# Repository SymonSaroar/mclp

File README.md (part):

# MCLP load-cell core

`mclp_core` is a load-cell weighing IP core for AMD FPGAs. It reads 1 to 64 Analog Devices AD7190 24-bit
sigma-delta ADCs in parallel, one per load cell, and computes the weight in the FPGA. The core decimates each
channel, corrects it for offset and gain, and trims it for its position on the platform. Then it sums the
channels and low-pass filters the sum. Software configures the core and reads the weight over AXI4-Lite. Raw
per-channel samples stream out over AXI4-Stream for calibration and diagnostics.

An optional inference engine runs a small int8 neural network on each weigh-in-motion load and corrects the
result. Software loads its models over AXI4-Lite at run time.

The repository also contains:

- A reference design for the AMD ZC702 evaluation board (Zynq-7000): Vivado block design, PetaLinux image,
  console application and REST/MQTT service
- An 8-channel AD7190 FMC card in KiCad: [hw/adc-card](hw/adc-card/README.md)
- cocotb unit tests, a system test with AD7190 models, and a DMA test of the reference design

Status: passes simulation at 1, 8 and 64 channels. Not tested on hardware yet.

## License

MCLP is available under the CERN Open Hardware Licence Version 2 - Strongly Reciprocal (hardware) and the
GPL-3.0 (software in `sw/`), or under a paid commercial license. See [LICENSE](LICENSE).

## Features

- Up to 64 channels
- Simultaneous sampling of all channels
- Up to 4800 samples/s per channel
- Weight output rate programmable up to 600 Hz
- Per-channel offset, gain and corner-trim calibration
- 64-tap FIR filter, coefficients reloadable at run time
- Stability detection
- Weigh-in-motion
- Int8 neural-network inference on each weigh-in-motion load, models loadable at run time
- Overload detection
- Per-channel fault detection: open wire, missing excitation, over-range, data errors
- Raw data capture, continuous or triggered
- Built-in self-test
- AXI4-Lite control interface
- AXI4-Stream raw data interface
- Interrupt output

## Supported devices and tools

- FPGA families declared in the IP package: Zynq-7000, Spartan-7, Artix-7, Kintex-7, Virtex-7, Kintex and
  Virtex UltraScale and UltraScale+, Zynq UltraScale+ MPSoC. Implemented and timed on `xc7z020clg484-1` only.
- Vivado 2025.1. The reference block-design script refuses other versions.
- Simulators: Vivado simulator, and Icarus Verilog 12 with the XPM models in `tb/common/xpm_models.sv`
- ADC: AD7190

## Resource utilization

`N_CH = 8`, `USE_NN = 1`, out-of-context synthesis, `xc7z020clg484-1`, Vivado 2025.1:

| LUT | LUT as memory | FF | Block RAM tiles | DSP48E1 |
|---|---|---|---|---|
| 5252 | 252 | 7319 | 18.5 (17 RAMB36, 3 RAMB18) | 23 |

Of that, the placed datapath of the inference engine takes 1641 LUTs, 758 FFs, 1 RAMB36, 1 RAMB18 and 10
DSP48E1. Its model memories are in the register file.

The reference design runs on the -1 speed grade with `aclk` at 100 MHz, `clk_spi` at 20 MHz and `clk_dsp` at
50 MHz. All user-specified timing constraints are met: WNS +0.737 ns, WHS +0.021 ns.

## Getting started

### Add the core to a Vivado project

1. Get the packaged core. Download `mclp_core-2.0.zip` from the [releases page](../../releases) and unzip it,
   or package it from this repository:

   ```sh
   vivado -mode batch -source tcl/package_ip.tcl      # writes build/ip_repo/mclp_core
   ```

2. Add the folder that holds `mclp_core` to the project's IP repositories (Settings > IP > Repository).
3. Add MCLP load-cell core to a block design. Set Channels (`N_CH`) and Inference engine (`USE_NN`).
4. Connect the interfaces:

   | Core | Connect to |
   |---|---|
   | `s_axi` | AXI4-Lite master, 64 KB address range |
   | `m_axis_raw` | AXI DMA S2MM, 64-bit stream. Optional. With `tready` low, the core drops raw records and the weight path keeps running. |
   | `aclk`, `aresetn` | AXI clock and its reset |
   | `clk_spi`, `clk_dsp`, `clk_locked` | MMCM outputs at 20 MHz and 50 MHz, and its `locked`. Reset the MMCM from the AXI reset. |
   | `irq` | Interrupt controller |
   | `spi_*`, `adc_sync_n` | FPGA pins to the AD7190s |

   [tcl/mclp_top_bd.tcl](tcl/mclp_top_bd.tcl) builds the reference block design with these connections.

5. Constrain the ADC pins: package pins, an I/O standard that matches the AD7190 DVDD, and the false paths in
   [xdc/mclp_timing.xdc](xdc/mclp_timing.xdc). The XPM macros inside the core carry their own clock-domain
   crossing constraints.
6. Write the software against the [register space](#register-space) and the
   [programming sequence](#programming-sequence). `sw/common` is a C implementation for bare metal and Linux.

### Prototype on the ZC702

The [reference design](#reference-design-zc702) runs the core with 8 channels on a ZC702 with the FMC card.
Each release has prebuilt boot files for it.

## Product specification

### Block diagram

### Parameters

| Parameter | Values | Default | Description |
|---|---|---|---|
| `N_CH` | 1 to 64 | 8 | Number of AD7190 chips, and the width of `spi_sdi` |
| `USE_NN` | 0, 1 | 1 | Inference engine and its model memories |

### Ports

| Port | Dir | Width | Clock | Description |
|---|---|---|---|---|
| `aclk` | in | 1 | | AXI clock |
| `aresetn` | in | 1 | async | Reset, active low |
| `clk_spi` | in | 1 | | 20 MHz: SPI master, sequencer, loopback emulator |
| `clk_dsp` | in | 1 | | 50 MHz: processing chain, raw capture |
| `clk_locked` | in | 1 | async | `clk_spi` and `clk_dsp` run. Holds their domains in reset while low. |
| `s_axi_*` | | | `aclk` | AXI4-Lite slave, 16-bit address, 32-bit data |
| `m_axis_raw_*` | out | 64 | `aclk` | AXI4-Stream master: `tdata`, `tlast`, `tvalid`, `tready` |
| `irq` | out | 1 | `aclk` | Interrupt, level, active high |
| `spi_sclk` | out | 1 | `clk_spi` | SPI clock, to SCLK of every AD7190 |
| `spi_sdo` | out | 1 | `clk_spi` | SPI data out, to DIN of every AD7190 |
| `spi_cs_n` | out | 1 | `clk_spi` | Chip select, to CS of every AD7190 |
| `adc_sync_n` | out | 1 | `clk_spi` | Filter reset, to SYNC of every AD7190 |
| `spi_sdi` | in | `N_CH` | async | SPI data in, bit k from DOUT/RDY of AD7190 k. Its falling edge marks data ready. |

### Clocks and resets

| Clock | Frequency | Logic |
|---|---|---|
| `aclk` | 100 MHz tested | AXI interfaces, registers, interrupt |
| `clk_spi` | 20 MHz required | SPI master, sequencer, loopback emulator, timestamps |
| `clk_dsp` | 50 MHz tested | CIC, scaling, sum, FIR, stability, weigh-in-motion, raw capture, inference |

SCLK is `clk_spi` / 8. A SYNC pulse lasts 32 `clk_spi` cycles (1.6 µs). The sequencer's `WAIT_US` counts 20
cycles per microsecond.

`aresetn` resets the `aclk` logic, and `clk_locked` resets the `clk_spi` and `clk_dsp` logic. Both are
asynchronous, and the core synchronizes them. Hold `clk_locked` low while `aresetn` is low. An MMCM reset
driven by the AXI reset does this.

### Data path

| Stage | Operation | Rate | Width |
|---|---|---|---|
| AD7190 | continuous conversion, sinc4, FS = 1, chop off | 4800 Hz | 24 data + 8 status |
| SPI receive | `N_CH` lanes in parallel, offset binary to two's complement | 4800 Hz | 24 |
| CIC | R = 8, N = 3, gain 256 per ADC code | 600 Hz | 32 |
| Gain/offset | `sat32(((x - OFFSET) * GAIN) >>> 30)` | 600 Hz | 32 |
| Trim | `sat32((x * TRIM) >>> 30)` | 600 Hz | 32 |
| Sum | exact sum of `N_CH` channels | 600 Hz | 40 |
| FIR | 64 taps, 18-bit coefficients, full precision | 600 Hz | 64 |
| Weight | `sat32(FIR >>> (20 + ceil(log2(N_CH))))` | 600 Hz | 32 |
| RESULT | every RESULT_DECIM-th weight | 50 Hz | 32 |

The default FIR is a 12 Hz Hamming-windowed sinc with taps summing to 2^20 (`coeff/fir64.py`). Its group
delay is 31.5 samples, 52.5 ms. At unity gain and trim, RESULT changes by 256 / 2^ceil(log2(N_CH)) counts per
ADC code on one channel: 32 at 8 channels. All channels at full scale fit in 32 bits.

The stability flag rises after STAB_COUNT consecutive weights within ±STAB_BAND of a reference. A weight
outside the band clears the flag and becomes the new reference.

A weigh-in-motion load starts with the first weight above WIM_ENTER and ends at the first weight below
WIM_EXIT. The core sums the load's weights that are at or above WIM_LEVEL times its peak. The ramps on and off
the platform drop out at any speed. The result is WIM_SUM / WIM_COUNT, one per load. The core holds the last
1024 weights of a load (1.7 s). In a longer load, it compares each older weight with the peak up to 1024
weights later.

### Register space

The register space is 64 KB. Offsets are from the base address that the block design assigns (0x43C0_0000 in
the reference design). Register map version 5. Each per-channel array takes one 64-word block, with channel k
at +4k.

| Offset | Name | Description |
|---|---|---|
| 0x000 | ID | 0x4D4C_05nn. [31:16] 0x4D4C ("ML"), [15:8] register map version, [7:0] `N_CH` |
| 0x004 | CTRL | [0] enable (reset 1), [1] loopback, [5:4] raw_tap, [6] raw_enable. Self-clearing: [2] fir_reload, [3] seq_start, [7] sw_trigger, [8] fault_clear |
| 0x008 | STATUS | [0] clocks locked, [1] seq_busy, [2] reload_busy, [3] overload, [4] stable, [5] capture_active |
| 0x00C | IRQ_STATUS | Write 1 to clear. [0] result, [1] stable, [2] weigh-in-motion, [3] overload, [4] fault, [5] sequencer done, [6] capture done, [7] inference done |
| 0x010 | IRQ_ENABLE | Same bits as IRQ_STATUS |
| 0x020 | RESULT | Weight, signed |
| 0x024 | RESULT_SEQ | Increments with each RESULT update |
| 0x028, 0x02C | WIM_SUM_LO, WIM_SUM_HI | Weigh-in-motion sum, 64 bit |
| 0x030 | WIM_COUNT | Weigh-in-motion weights summed |
| 0x034 | STAB_BAND | Reset 4096 |
| 0x038 | STAB_COUNT | Reset 60 |
| 0x03C, 0x040 | WIM_ENTER, WIM_EXIT | Reset 0x7FFF_FFFF (off) |
| 0x048 | RESULT_DECIM | Reset 12 |
| 0x04C | TRIG_CFG | [1:0] mode: 0 continuous, 1 one-shot, 2 threshold. [31:16] frames per one-shot |
| 0x050 | TRIG_THRESHOLD | Sum level that starts a mode 2 capture |
| 0x054 | LOOPBACK_CFG | [0] ramp, [1] inject ERR, [2] inject parity error, [9:4] channel for injection, [31:16] frame period in `clk_spi` cycles (reset 4166) |
| 0x058 | LOOPBACK_VALUE | Constant-mode data, reset 0x123456 |
| 0x05C | WIM_LEVEL | [15:0] share of the load's peak, Q0.16. Reset 0xEE14 (0.93) |
| 0x200-0x2FC | FIR | 64 coefficients, word i applies to x[n-i]. Reset from `coeff/fir64.mem` |
| 0x400-0x7FC | SEQ | Sequencer RAM, 256 words. Reset from `coeff/seq_init.mem` |
| 0x800-0x8FC | SEQ_RESP[64] | Last XFER read per chip |
| 0x900-0x9FC | GAIN[64] | Q2.30, reset 1.0 |
| 0xA00-0xAFC | OFFSET[64] | CIC units, reset 0 |
| 0xB00-0xBFC | TRIM[64] | Q2.30, reset 1.0 |
| 0xC00-0xCFC | FAULT[64] | Sticky. [0] ERR, [1] NOREF, [2] parity error, [3] stale (RDY set), [4] loopback mismatch |
| 0x1000 | NN_CTRL | [0] enable: run the model after each weigh-in-motion load. Reset 0 |
| 0x1004 | NN_STATUS | [0] busy |
| 0x1008 | NN_SEQ | Increments with each inference |
| 0x100C | NN_EST | Corrected weigh-in-motion estimate, weight counts, signed |
| 0x1010 | NN_CORR | Correction to WIM_SUM / WIM_COUNT, Q0.20, signed |
| 0x1014 | NN_CYCLES | `clk_dsp` cycles of the last inference |
| 0x2000-0x20FC | NN_LAYER[64] | Layer list. Reset from `coeff/nn_layers.mem` |
| 0x3000-0x33FC | NN_BIAS[256] | Biases, int32. Reset from `coeff/nn_bias.mem` |
| 0x4000-0x7FFC | NN_WEIGHT[4096] | Weights, four int8 per word, the first in [7:0]. Reset from `coeff/nn_weights.mem` |

Unmapped addresses and array entries at or above `N_CH` read 0x0BAD_0BAD. With `USE_NN = 0`, 0x1000 to 0x7FFF
read 0x0BAD_0BAD too. A configuration write reaches `clk_spi` and `clk_dsp` within about 1 µs.

Fault flags:

- ERR is the AD7190's error bit: over-range, an open input with the burnout currents on, or a missing
  reference when REFDET is on.
- NOREF is its reference-detect bit.
- A parity error is a corrupted word on the cable.
- Stale means that the chip's conversion was not complete when the core read it.

A new flag sets IRQ_STATUS[4]. CTRL.fault_clear clears all flags.

### Sequencer

The sequencer drives the shared SPI lines from a command list in its RAM. It runs the list from word 0 after
reset, on CTRL.seq_start, and on a rising edge of CTRL.enable. Each command is two words:

```
w0 = {op[3:0], ntx[5:0], nrx[5:0], arg[15:0]}
w1 = data shifted out, MSB first
```

| op | Command | Action |
|---|---|---|
| 0 | END | Stop |
| 1 | XFER | Shift `ntx` bits of `w1` out, then read `nrx` bits from every chip into SEQ_RESP |
| 2 | SYNC | SYNC low for 1.6 µs |
| 3 | WAIT_US | Wait `arg` µs |
| 4 | WAIT_RDY | Wait for DOUT/RDY low on chip 0 |
| 5 | STREAM | Read a 32-bit word (data + status) from every chip on each DOUT/RDY falling edge |

STATUS.seq_busy falls and IRQ_STATUS[5] sets when the list reaches END or STREAM.

The default list (`coeff/seq_init.py`) resets the chips, reads their ID registers and writes the
configuration. Then it runs the internal zero-scale calibration, starts continuous conversion, pulses SYNC
and streams. The AD7190 configuration is AIN1/AIN2, REFIN1, reference detect on, buffer on, bipolar and gain
128. The clock and filter settings are the external clock on MCLK2, sinc4 and FS = 1, with the status byte
and parity appended to each word. To leave continuous read, run `WAIT_RDY`, then an `XFER` of 0x58 with
`ntx = 8`, `nrx = 32`.

### Raw records

CTRL.raw_tap selects the source: 0 ADC code (24 bit, sign-extended), 1 CIC output, 2 after gain/offset, 3
after trim. Each frame becomes one record of 2 + ceil(`N_CH` / 2) 64-bit words, with `tlast` on the last word.
A record is 48 bytes at 8 channels and 272 bytes at 64.

| Word | Content |
|---|---|
| 0 | [63:16] timestamp in `clk_spi` cycles at the DOUT/RDY edge, [15:14] tap, [13:0] 0 |
| 1 to ceil(`N_CH` / 2) | Samples `{ch1, ch0}`, `{ch3, ch2}` and so on, with `{0, chN-1}` last when `N_CH` is odd |
| last | Fault word: bit k set when channel k had a fault flag in this frame |

At tap 0, the timestamp and the fault word belong to the record's own frame. At taps 1 to 3, they come from
the newest complete frame. The core starts a record at channel 0 only when the output FIFO has room for the
whole record. Otherwise it skips the record.

Trigger modes (TRIG_CFG[1:0]):

- 0: continuous while CTRL.raw_enable is set.
- 1: a one-shot of TRIG_CFG[31:16] records after CTRL.sw_trigger.
- 2: a one-shot that CTRL.sw_trigger arms. It starts at the first frame whose sum exceeds TRIG_THRESHOLD.

IRQ_STATUS[6] sets when a one-shot ends.

### Inference engine

With `USE_NN = 1`, the core runs a small neural network on each weigh-in-motion load and corrects the result.
The engine starts when a load ends and NN_CTRL.enable is set. It skips a load that ends while it is busy.

The input is every 4th weight up to the load's exit sample: 256 weights, 1.7 s. Each weight x enters as its
deviation from the core's own result, ref = WIM_SUM / WIM_COUNT. The int8 input value is
(x / ref - 1) x 1024, saturated. In integers:

- ref is the quotient WIM_SUM / WIM_COUNT, clamped to 1 to 2^31 - 1.
- k is the bit length of ref, and R = 2^(k+21) / ref.
- d = x - ref, clamped to ±2^k.
- q = sat8((d x R + 2^(k+10)) >> (k+11)).

The network is a list of one-dimensional convolutions over the valid positions. Weights and activations are
int8, and biases are int32. A dense layer is a convolution whose kernel spans its whole input. Hidden layers
requantize to int8 as (acc x M + 2^(s-1)) >> s, with a 15-bit M, and clip at 0 when the layer has a ReLU. The
last layer's M and s scale its accumulator the same way to NN_CORR, a correction in Q0.20 saturated to 32
bits. The engine then computes NN_EST = ref + (ref x NN_CORR + 2^19) >> 20, saturated to 32 bits.

The engine does one multiply-accumulate per `clk_dsp` cycle. The default model takes 44439 cycles (0.89 ms at
50 MHz). IRQ_STATUS[7] sets when the result is in the registers.

The layer list has four words per layer, from NN_LAYER[0] to the layer marked last.

| Word | Fields |
|---|---|
| 0 | [31] last, [30] ReLU, [29:26] stride, [25:16] kernel K, [15:8] input channels C, [7:0] output channels O |
| 1 | [25:16] input length L, [9:0] output length T = (L - K) / stride + 1 |
| 2 | [21:16] s, 1 to 47, and [14:0] M |
| 3 | [31:16] first bias, [15:0] first weight byte |

Weights are in (O, C, K) order. The engine stores a layer's input and output channel by channel, so C x L and
O x T must not exceed 1024. The first layer has C = 1 and L = 256. A model has at most 16 layers, 256 biases
and 16384 weight bytes. Every accumulator must fit 48 bits.

To load a model:

1. Clear NN_CTRL.enable.
2. Write NN_LAYER, NN_BIAS and NN_WEIGHT.
3. Set NN_CTRL.enable.

The memories start with the default model in `coeff/nn_*.mem`. It corrects weigh-in-motion results for single
axles on a 0.75 m platform with 8 cells. Another installation needs a model trained for it.

### Loopback BIST

With CTRL.loopback set, an AD7190 emulator drives the DOUT inputs. It answers the core's own SCLK, CS and
SYNC with AD7190 continuous-read timing. It sends 32-bit words with a status byte and parity. Channel k sends
`LOOPBACK_VALUE + (k << 16)`, or a frame counter plus `k << 16` in ramp mode. LOOPBACK_CFG injects an ERR bit
or a parity error on one channel.

A checker compares each received word with the emulator's word and sets
FAULT[k] bit 4 on a mismatch. With a constant pattern, software can predict RESULT and the raw records bit for
bit from the coefficients.

### Programming sequence

1. Read ID. Check that [31:8] is 0x4D4C05 and take `N_CH` from [7:0].
2. Wait for STATUS[0] (clocks locked) and IRQ_STATUS[5] (sequencer done). After reset, the core runs the
   default list on its own.
3. Check the AD7190 ID answers: SEQ_RESP[k] bits [3:0] read 0x4 for each chip k below `N_CH`.
4. Write OFFSET[k], GAIN[k] and TRIM[k] for each channel.
5. Optional: write 64 FIR coefficients, pulse CTRL.fir_reload and wait until STATUS[2] (reload_busy) clears.
   The new set takes over between two samples.
6. Write IRQ_ENABLE. On the interrupt, read IRQ_STATUS, write the set bits back to clear them, and read
   RESULT and RESULT_SEQ.
7. Convert RESULT to mass in software: `(RESULT - zero) * span`.
8. Optional, weigh-in-motion: write WIM_ENTER, WIM_EXIT and WIM_LEVEL. On IRQ_STATUS[2], WIM_SUM / WIM_COUNT is
   the load's weight in RESULT units.
9. Optional, inference: load a model ([Inference engine](#inference-engine)) and set NN_CTRL.enable. On
   IRQ_STATUS[7], NN_EST is the corrected weight of the same load, also in RESULT units.

To rerun the default list or run another one:

1. Write the list to SEQ.
2. Write 1 to IRQ_STATUS[5].
3. Pulse CTRL.seq_start.
4. Wait for IRQ_STATUS[5].

The calibration in `sw/common/calib.c` takes the offsets from 1 s of CIC data at no load. It takes the corner
trims from a test weight placed over each cell in turn (regularized least squares), and the span from the
test weight's mass.

### Connecting the AD7190s

- One 4.9152 MHz CMOS oscillator drives MCLK2 on every AD7190. MCLK1 stays open. The chips then convert in
  lockstep from the shared SYNC.
- SCLK, DIN, CS_N and SYNC_N go to every chip. Buffer them for more than a few loads. The reference card
  drives four chips from one 74AHC244 output.
- DOUT/RDY of chip k goes to `spi_sdi[k]`.
- DVDD equals the VCCO of the FPGA bank, or the lines need level translators.
- The bridge excitation feeds REFIN1(+) and REFIN1(-) for a ratiometric measurement.
- Input filter per channel: 100 Ω in series per line, 0.1 µF across the pair, 0.01 µF from each line to
  AGND (AD7190 data sheet, p. 38).

## Simulation

Each RTL module has a cocotb unit test on Icarus Verilog, in its own folder. Each test checks its module
against a Python model and builds the module in `build/tb/<module>/`.

```sh
python tb/afe_frontend/test_afe_frontend.py         # one module
for t in tb/*/test_*.py; do python "$t"; done       # all
```

The system test runs `mclp_core` with one AD7190 model per channel, for about 420 ms of simulated time. It
covers:

- the init list
- bit-exact records at taps 0 and 3
- static weight, stability and the result interrupt
- overload
- the loopback BIST with ERR injection
- the burnout and reference self-test
- the inference engine on a weigh-in-motion load
- FIR reload

It ends with `SYSTEM TEST PASSED` or `FAILED`. It runs in the Vivado simulator (Run Simulation in the
project) or in Icarus:

```sh
mkdir -p build/tb/system && cp coeff/*.mem build/tb/system/
iverilog -g2012 -s mclp_top_tb -o build/tb/system/sys.vvp tb/system/*.sv rtl/*.sv tb/common/xpm_models.sv
cd build/tb/system && vvp -n sys.vvp
```

`-P mclp_top_tb.N_CH=64` on the `iverilog` line runs it at another channel count. At 64 channels, the run
takes about 45 minutes.

The DMA test runs the reference block design with the PS7 verification IP in the Vivado simulator. It checks
the ID, then sends one raw record from the core through the AXI DMA into DDR.

```sh
vivado -mode batch -source tcl/mclp.tcl -tclargs --project_name mclp_dma --sim dma --simulate
```

The calibration math in `sw/common` (FIR design, corner trim solver, Q2.30, checksum) runs on the PC:

```sh
gcc -O2 -Isw/common -o build/test_calib sw/common/test/test_calib.c sw/common/calib.c -lm
build/test_calib
```

## Reference design: ZC702

`tcl/mclp_top_bd.tcl` builds the block design `mclp_top` on the ZC702 (`xc7z020clg484-1`):

| Block | Configuration |
|---|---|
| `processing_system7_0` | ZC702 preset, FCLK0 100 MHz, GP0, HP0, IRQ_F2P |
| `smartconnect_0` | GP0 to the core's registers and the DMA control port |
| `axi_dma` | S2MM, scatter-gather, control at 0x4040_0000 |
| `smartconnect_1` | DMA descriptors and data to HP0 |
| `clk_wiz` | 20 MHz and 50 MHz from FCLK0, reset by the PS reset |
| `mclp_core_0` | `N_CH = 8`, registers at 0x43C0_0000 |
| `irq_concat` | IRQ_F2P[0] DMA, IRQ_F2P[1] core |

Placed and routed, the whole design takes 9783 LUTs, 14190 FFs, 20 block RAM tiles and 23 DSP48E1.

### Hardware

- ZC702 evaluation board (EK-Z7-ZC702-G) with its 12 V supply and USB cables
- ADC card with eight AD7190 on an FMC LPC connector: [hw/adc-card](hw/adc-card/README.md)
- Eight bridge load cells
- microSD card, 4 GB or larger
- For the one-time VADJ change: TI USB Interface Adapter (USB-TO-GPIO or USB-TO-GPIO2) and a Windows PC with
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
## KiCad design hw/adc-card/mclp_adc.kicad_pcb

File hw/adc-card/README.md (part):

# ADC card: reference design

This card is the analog front end for MCLP. It carries eight AD7190 24-bit ΔΣ ADCs, one per load cell, on an
FMC LPC mezzanine that plugs into FMC1 (J3) of the ZC702. This folder holds the design: this specification,
the KiCad schematic and board, and the files that a board house needs to make and assemble it.

Status: schematic and 4-layer layout in KiCad 10. The schematic is checked against the FPGA pin constraints
and the AD7190 pin table. The card is a reference for the MCLP IP. No card is built, and nothing is tested on
hardware.

## Files

| File | Content |
|---|---|
| `mclp_adc.kicad_pro` | KiCad project: open this |
| `mclp_adc.kicad_sch` | root sheet: interface, power and the eight channel sheets |
| `interface.kicad_sch` | FMC connector, FRU EEPROM, clock and SPI distribution |
| `power.kicad_sch` | buck converter, LDOs, DVDD filter |
| `channel.kicad_sch` | one load-cell channel, used eight times (sheets CH0 to CH7) |
| `mclp_adc.kicad_sym`, `sym-lib-table` | project symbols: AD7190, FMC LPC connector |
| `mclp_adc.kicad_pcb` | board: 184 × 100 mm, 4 layers |
| `mclp_adc.kicad_jobset` | checks and fabrication outputs, run from KiCad ([Manufacture](#manufacture)) |
| `fab/mclp_adc-gerbers.zip` | Gerber and drill files for the board house |
| `fab/mclp_adc-bom.csv` | bill of materials, grouped by value, footprint and part number |
| `fab/mclp_adc-all-pos.csv` | position of every part to place, both sides (J1 on the bottom) |
| `fab/mclp_adc-schematic.pdf` | schematic, for reading without KiCad |

- All footprints come from KiCad 10's standard libraries. Nothing else needs installing.
- Each chip sits in a dashed box, wired to its own resistors and capacitors. Boxes and sheets connect through
  net labels: pins and wires with the same label are on the same net.
- Reference designators: interface 1 to 39, power 50 to 69, channel k in the hundreds k + 1 (CH0: U101, J101,
  R101 and up). The channel sheets are instances of one sheet. KiCad's multichannel tools (rule areas from
  sheets, then repeat layout) can therefore copy one placed and routed channel to the other seven.

## Overview

```
 FMC LPC (J1)                                                             front edge
 12P0V ──► TPS54202 buck 6.0 V ──► ADP7118 5.0 V ─┬─ AVDD ───────────────► 8 × AD7190 AVDD
                                                  └─ net tie ── EXC_5V ──► 8 × polyfuse ──► EXC+ of each cell
 VADJ (3.3 V) ── ferrite ── DVDD ──► 8 × AD7190 DVDD, buffers, oscillator
 3P3VAUX ──► FRU EEPROM (I2C)

 LA00_P/N, LA01_P/N ── SCLK, DIN, CS_N, SYNC_N ──► 74AHC244 ──► group A (ADC 0..3), group B (ADC 4..7)
 4.9152 MHz oscillator ──► 74AHC244 (1 in, 8 out) ──► MCLK2 of ADC 0..7
 LA02..LA05 P/N ◄── DOUT/RDY of ADC 0..7

 per channel n:  7-pin terminal block ── ESD ── RC filters ── AD7190 #n
                 EXC+  SENSE+  SIG+  SIG-  SENSE-  EXC-  SHIELD
```

- 6-wire load cells: the AD7190 takes its reference from the sense lines at the cell, so the cable's resistance
  and its drift drop out of the ratio. Two solder jumpers per channel tie sense to excitation for 4-wire cells.
- Ratiometric: excitation and reference come from the same source, so excitation drift and noise cancel. AVDD
  comes from the same regulator, so the reference can never sit above AVDD.
- All eight converters run from one 4.9152 MHz oscillator and one SYNC line, so they sample together.

## Mechanical

- Connector J1: Samtec FMC LPC mezzanine connector, footprint
  `Connector_Samtec:Samtec_FMC_ASP-134604-01_4x40_Vertical` in KiCad 10. ZC702 users report mating J3 with the
  ASP-134604 series. Listings disagree on its gender, and the suffix sets the stack height (10 mm clears the
  ZC702's parts near J3). Check the Samtec drawing against the ZC702's J3 part before you build the card.
- The card is 184 × 100 mm, larger than the VITA 57.1 single-width outline. J1 is on the left edge. Four
  7-pin terminal blocks (24.5 mm each at 3.5 mm pitch) are on the top edge and four on the bottom edge. Before
  you build the card, check the outline against the ZC702 around J3 (mounting holes, heat sink, other
  connectors).
- Mount the card with the FMC standoffs. The terminal blocks take cable force, so add a support standoff near
  the front edge.

## FMC connections

| Signal | J1 pin | FPGA (ZC702 bank 34) | Card net |
|---|---|---|---|
| LA00_CC_P | G6 | K19 | SCLK (FPGA out) |
| LA00_CC_N | G7 | K20 | DIN (FPGA out) |
| LA01_CC_P | D8 | N19 | CS_N (FPGA out) |
| LA01_CC_N | D9 | N20 | SYNC_N (FPGA out) |
| LA02_P, LA02_N | H7, H8 | L21, L22 | DOUT0, DOUT1 |
| LA03_P, LA03_N | G9, G10 | J20, K21 | DOUT2, DOUT3 |
| LA04_P, LA04_N | H10, H11 | M21, M22 | DOUT4, DOUT5 |
| LA05_P, LA05_N | D11, D12 | N17, N18 | DOUT6, DOUT7 |

| Pin | Use on the card |
|---|---|
| 12P0V (C35, C37) | buck input, 1 A maximum per VITA 57.1 |
| VADJ (G39, H40) | DVDD 3.3 V: the ZC702's VADJ must be set to 3.3 V (main README, Set VADJ to 3.3 V) |
| 3P3VAUX (D32) | FRU EEPROM supply |
| 3P3V (C39, D36, D38, D40) | not used |
| GND (all GND pins) | ground plane |
| PRSNT_M2C_L (H2) | to GND: tells the carrier a card is present |
| TDI (D30), TDO (D31) | linked by R1, 0 Ω: the ZC702 switches the FMC into its JTAG chain when a card is present (UG850, FMC Connector JTAG Bypass) |
| SCL (C30), SDA (C31) | FRU EEPROM U1, 24AA02 in SOT-23: fixed address 0x50, WP to GND. The carrier has the pull-ups. |
| PG_C2M (D1), GA0 (C34), GA1 (D35), TCK, TMS, TRST_L, VREF_A_M2C, CLK0/1_M2C, DP0, GBTCLK0, other LA pins | not connected |

## Power

| Rail | Source | Load | Notes |
|---|---|---|---|
| 6V0 | TPS54202 buck from 12P0V | about 170 mA | intermediate rail for the LDO, which filters its ripple |
| AVDD | ADP7118 U51, 5.0 V | 8 × 6.75 mA = 54 mA maximum | AD7190 analog supply |
| EXC_5V | AVDD through the net tie NT50 | 8 × 14.3 mA = 114 mA with 350 Ω cells | bridge excitation and, through the sense lines, the reference |
| DVDD | VADJ through a ferrite bead | about 15 mA | AD7190 digital supply, buffers, oscillator |

Buck U50 (values from the TPS54202 data sheet, Table 7-2 and section 7.2.3, adapted to 6 V):

- Feedback: 100 kΩ (top) and 11.0 kΩ (bottom), VOUT = 0.596 V × (100/11 + 1) = 6.01 V (5.86 to 6.17 V over the
  reference tolerance). The LDOs need at most 0.42 V of dropout at 200 mA, so 5.86 V still leaves margin.
- Inductor 22 µH, saturation current 1 A or more, shielded. Ripple at 12 V in: 0.27 A peak to peak.
- Output 2 × 22 µF ceramic (X7R or X5R, 16 V), 75 pF across the top feedback resistor.
- Input 10 µF + 100 nF ceramic, 25 V or more. Bootstrap 100 nF between BOOT and SW. EN left open (internal
  pull-up).

LDO U51 (ADP7118, LFCSP-6, fixed 5.0 V) feeds AVDD and the excitation. Confirm its ordering code in ADI's data
sheet. It has 2.2 µF ceramic at input and output, a 1 nF soft-start capacitor on SS, and EN tied to VIN. Its
load is 114 + 54 = 168 mA of the ADP7118's 200 mA.

The AD7190 works with a reference from 1 V up to AVDD. With excitation and AVDD from two regulators, their
tolerances could put the reference, which comes from the excitation, above AVDD. The net tie NT50 at the output
capacitor C57 is the star point. AVDD and EXC_5V leave it as separate traces. A shorted cell pulls AVDD down
too, until its polyfuse trips. The converters may then reset, and the firmware reports the fault.

Budget: 170 mA at 6 V is about 1 W. Through the buck at roughly 85%, that is about 0.1 A from 12P0V.

Test points:

- TP50 to TP54 on 12P0V, 6V0, EXC_5V, AVDD, DVDD
- TP1 to TP5 on OSC_OUT, MCLK0, SCLK_A, CS_A_N, DOUT0
- TP6, TP55, TP56 on ground (through-hole, for a wire loop)

## Clock and SPI distribution

- X1: 4.9152 MHz 3.3 V CMOS oscillator (Abracon ASE series, 3.2 × 2.5 mm), 100 nF decoupling.
- U2: 74AHC244 with all eight inputs tied to X1 and both OE low. Each output drives one MCLK2 through 33 Ω (R10
  to R17). MCLK1 stays open, because the firmware selects an external clock on MCLK2.
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
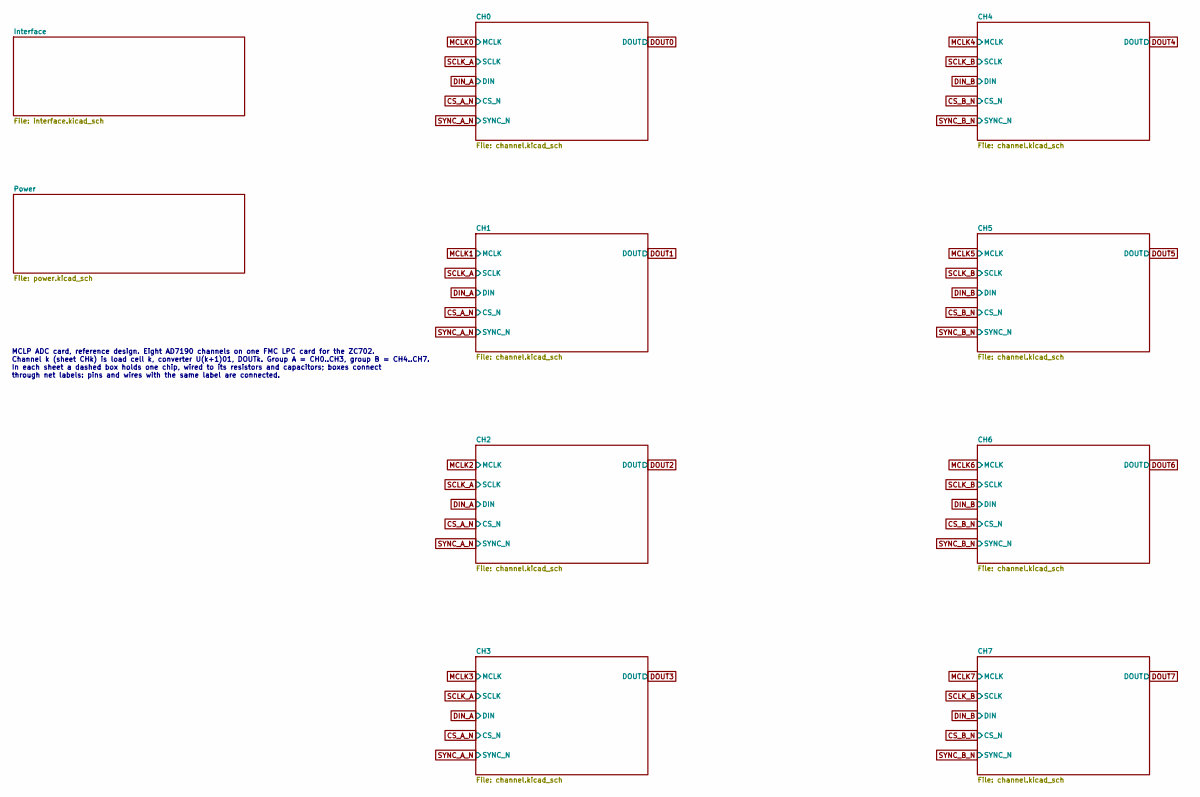
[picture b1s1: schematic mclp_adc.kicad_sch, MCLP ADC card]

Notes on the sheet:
MCLP ADC card, reference design. Eight AD7190 channels on one FMC LPC card for the ZC702. Channel k (sheet CHk) is load cell k, converter U(k+1)01, DOUTk. Group A = CH0..CH3, group B = CH4..CH7. In each sheet a dashed box holds one chip, wired to its resistors and capacitors; boxes connect through 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

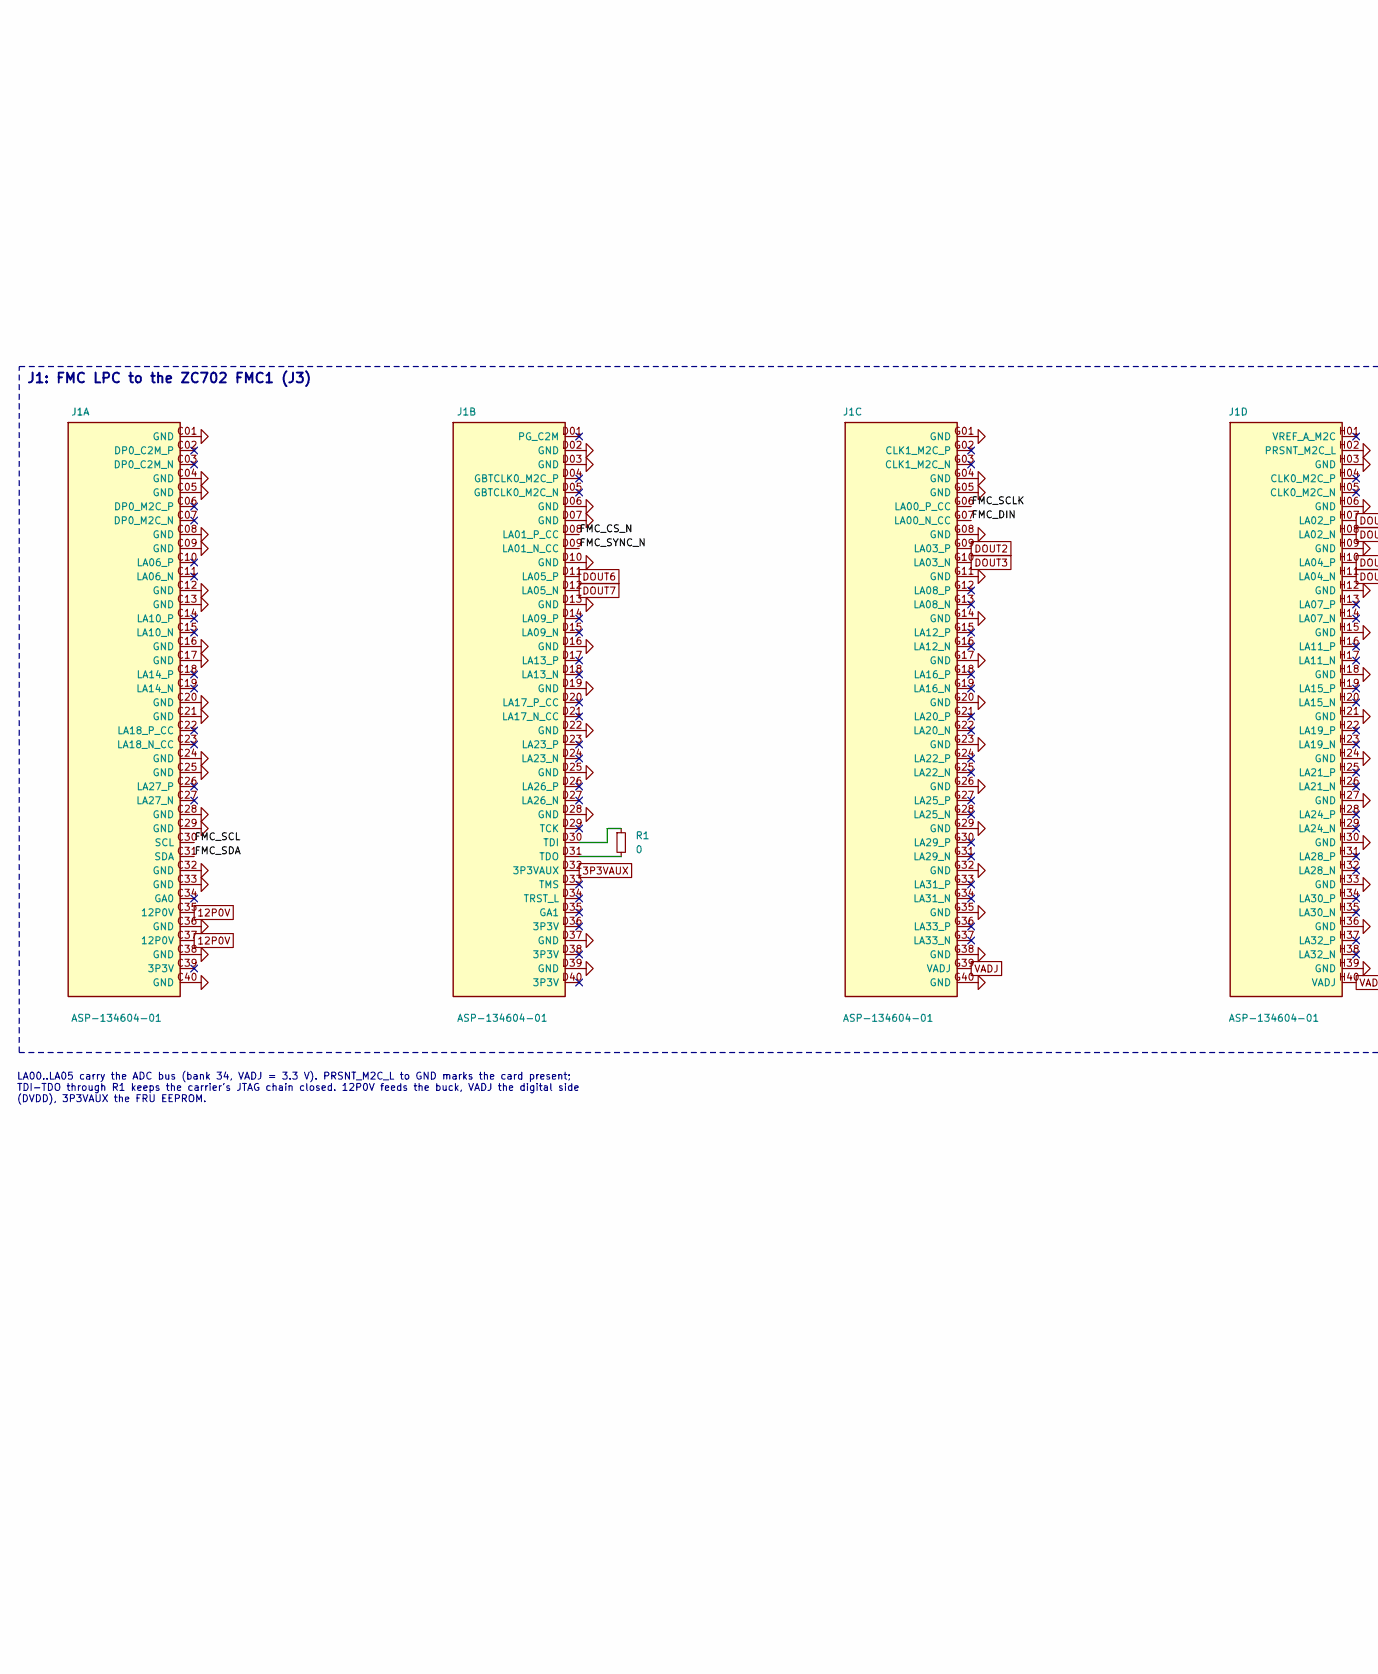
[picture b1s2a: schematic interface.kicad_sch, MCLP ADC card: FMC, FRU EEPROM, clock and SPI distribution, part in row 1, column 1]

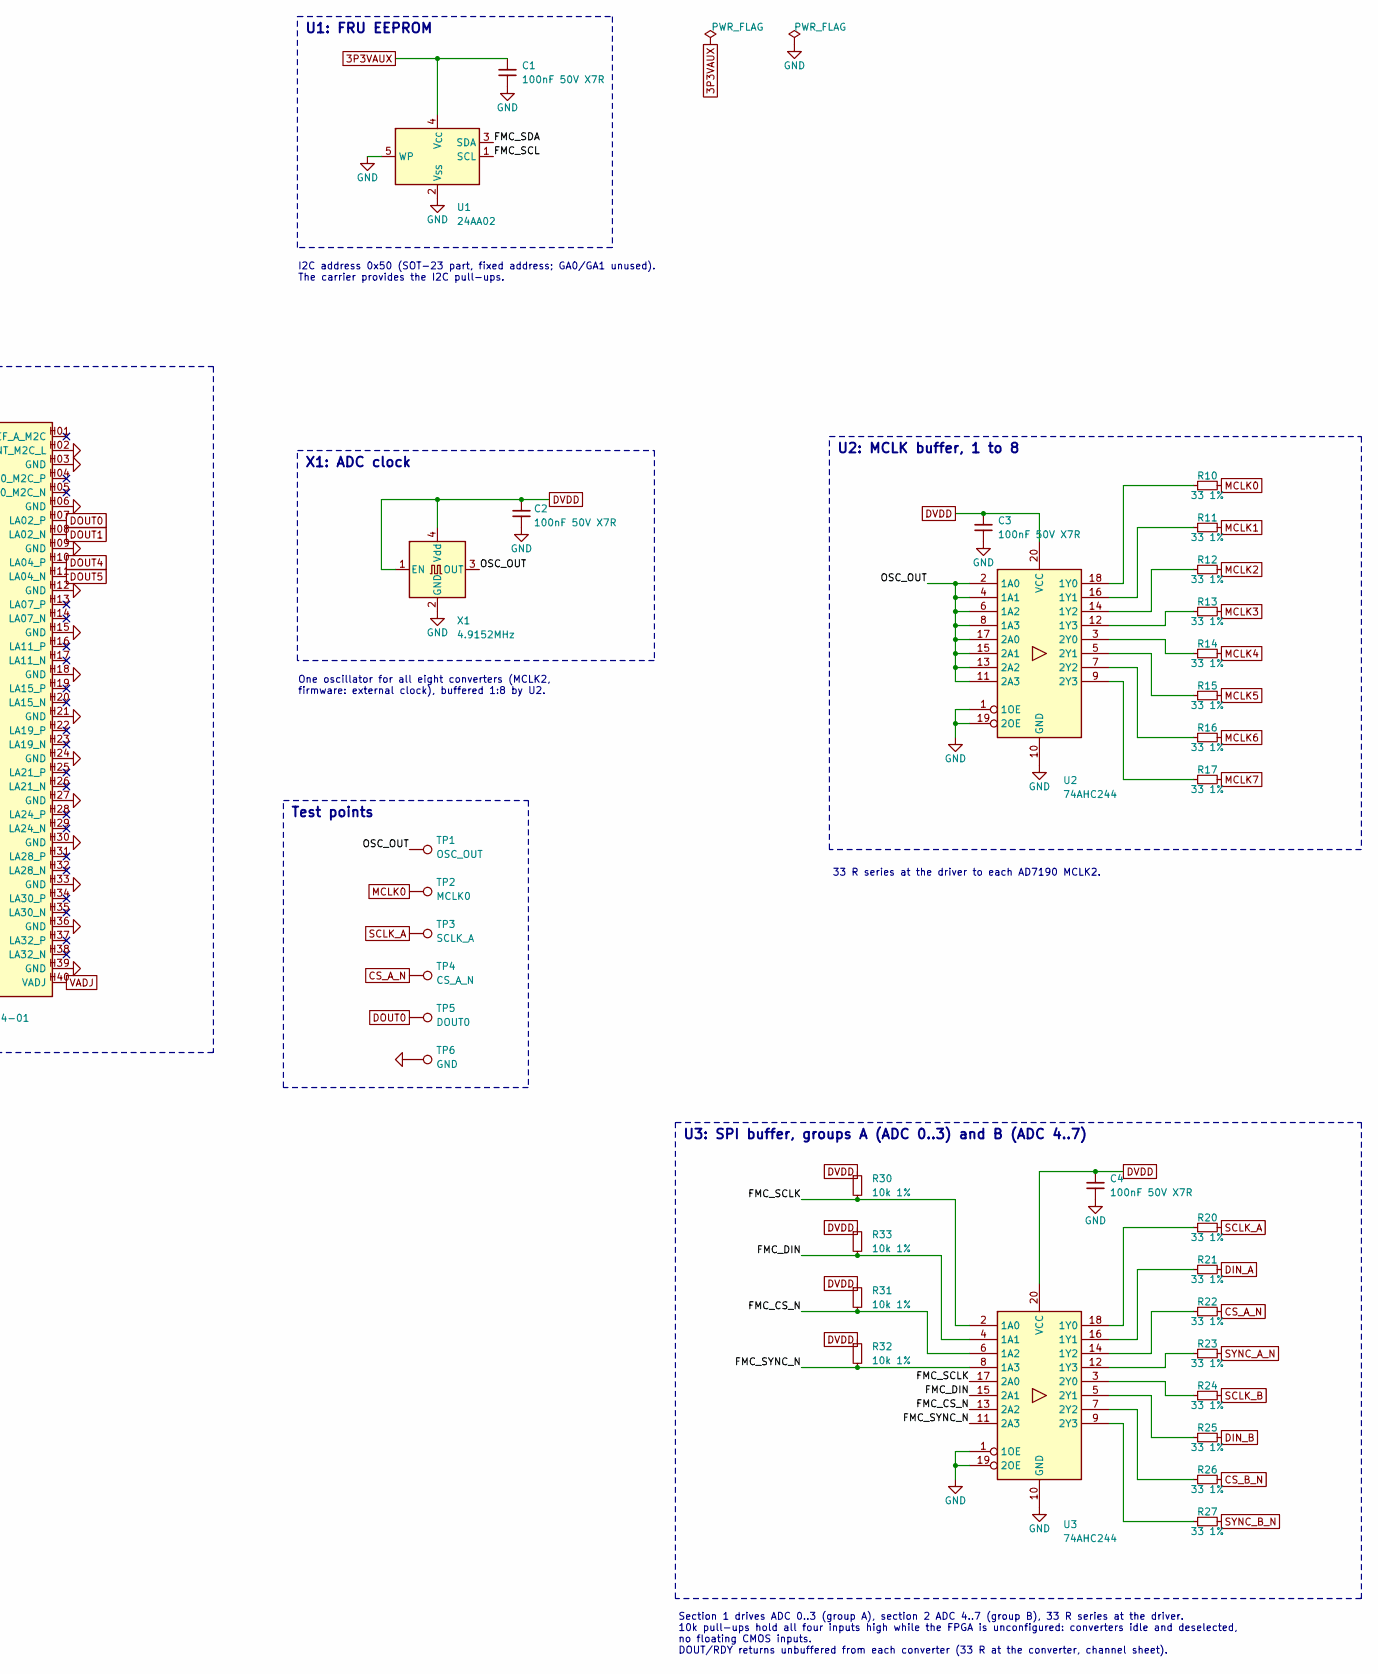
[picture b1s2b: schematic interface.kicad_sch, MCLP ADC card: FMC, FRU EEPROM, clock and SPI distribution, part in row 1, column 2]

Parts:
C1, C2, C3, C4: 100nF 50V X7R; C_0603_1608Metric
J1: ASP-134604-01; Samtec_FMC_ASP-134604-01_4x40_Vertical; MPN Samtec ASP-134604-01 (check gender and 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
R1: 0; R_0603_1608Metric
R10, R11, R12, R13, R14, R15, R16, R17, R20, R21, R22, R23, R24, R25, R26, R27: 33 1%; R_0603_1608Metric
R30, R31, R32, R33: 10k 1%; R_0603_1608Metric
TP1: OSC_OUT; TestPoint_Pad_D1.5mm
TP2: MCLK0; TestPoint_Pad_D1.5mm
TP3: SCLK_A; TestPoint_Pad_D1.5mm
TP4: CS_A_N; TestPoint_Pad_D1.5mm
TP5: DOUT0; TestPoint_Pad_D1.5mm
TP6: GND; TestPoint_THTPad_D2.0mm_Drill1.0mm
U1: 24AA02; SOT-23-5; MPN Microchip 24AA02T-I/OT
U2, U3: 74AHC244; TSSOP-20_4.4x6.5mm_P0.65mm; MPN TI SN74AHC244PWR
X1: 4.9152MHz; Oscillator_SMD_Abracon_ASE-4Pin_3.2x2.5mm; MPN Abracon ASE series, 4.9152 MHz, 3.3 V C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

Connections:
3P3VAUX: C1.1, J1.D32 (3P3VAUX), U1.4 (V_{CC})
12P0V: J1.C35 (12P0V), J1.C37 (12P0V); also elsewhere on the board
/Interface/FMC_CS_N: J1.D08 (LA01_P_CC), R31.2, U3.6 (1A2), U3.13 (2A2)
/Interface/FMC_DIN: J1.G07 (LA00_N_CC), R33.2, U3.4 (1A1), U3.15 (2A1)
/Interface/FMC_SCL: J1.C30 (SCL), U1.1 (SCL)
/Interface/FMC_SCLK: J1.G06 (LA00_P_CC), R30.2, U3.2 (1A0), U3.17 (2A0)
/Interface/FMC_SDA: J1.C31 (SDA), U1.3 (SDA)
/Interface/FMC_SYNC_N: J1.D09 (LA01_N_CC), R32.2, U3.8 (1A3), U3.11 (2A3)
/Interface/OSC_OUT: TP1.1 (1_1), U2.2 (1A0), U2.4 (1A1), U2.6 (1A2), U2.8 (1A3), U2.11 (2A3), U2.13 (2A2), U2.15 (2A1), U2.17 (2A0), X1.3 (OUT)
CS_A_N: R22.2, TP4.1 (1_1); also elsewhere on the board
CS_B_N: R26.2; also elsewhere on the board
DIN_A: R21.2; also elsewhere on the board
DIN_B: R25.2; also elsewhere on the board
DOUT0: J1.H07 (LA02_P), TP5.1 (1_1); also elsewhere on the board
DOUT1: J1.H08 (LA02_N); also elsewhere on the board
DOUT2: J1.G09 (LA03_P); also elsewhere on the board
DOUT3: J1.G10 (LA03_N); also elsewhere on the board
DOUT4: J1.H10 (LA04_P); also elsewhere on the board
DOUT5: J1.H11 (LA04_N); also elsewhere on the board
DOUT6: J1.D11 (LA05_P); also elsewhere on the board
DOUT7: J1.D12 (LA05_N); also elsewhere on the board
DVDD: C2.1, C3.1, C4.1, R30.1, R31.1, R32.1, R33.1, U2.20 (VCC), U3.20 (VCC), X1.1 (EN), X1.4 (Vdd); also elsewhere on the board
GND: C1.2, C2.2, C3.2, C4.2, J1.C01 (GND), J1.C04 (GND), J1.C05 (GND), J1.C08 (GND), J1.C09 (GND), J1.C12 (GND), J1.C13 (GND), J1.C16 (GND), J1.C17 (GND), J1.C20 (GND), J1.C21 (GND), J1.C24 (GND), J1.C25 (GND), J1.C28 (GND), J1.C29 (GND), J1.C32 (GND), J1.C33 (GND), J1.C36 (GND), J1.C38 (GND), J1.C40 (GND), J1.D02 (GND), J1.D03 (GND), J1.D06 (GND), J1.D07 (GND), J1.D10 (GND), J1.D13 (GND), J1.D16 (GND), J1.D19 (GND), J1.D22 (GND), J1.D25 (GND), J1.D28 (GND), J1.D37 (GND), J1.D39 (GND), J1.G01 (GND), J1.G04 (GND), J1.G05 (GND), J1.G08 (GND), J1.G11 (GND), J1.G14 (GND), J1.G17 (GND), J1.G20 (GND), J1.G23 (GND), J1.G26 (GND), J1.G29 (GND), J1.G32 (GND), J1.G35 (GND), J1.G38 (GND), J1.G40 (GND), J1.H02 (PRSNT_M2C_L), J1.H03 (GND), J1.H06 (GND), J1.H09 (GND), J1.H12 (GND), J1.H15 (GND), J1.H18 (GND), J1.H21 (GND), J1.H24 (GND), J1.H27 (GND), J1.H30 (GND), J1.H33 (GND), J1.H36 (GND), J1.H39 (GND), TP6.1 (1_1), U1.2 (V_{SS}), U1.5 (WP), U2.1 (1OE), U2.10 (GND), U2.19 (2OE), U3.1 (1OE), U3.10 (GND), U3.19 (2OE), X1.2 (GND); also elsewhere on the board
MCLK0: R10.2, TP2.1 (1_1); also elsewhere on the board
MCLK1: R11.2; also elsewhere on the board
MCLK2: R12.2; also elsewhere on the board
MCLK3: R13.2; also elsewhere on the board
MCLK4: R14.2; also elsewhere on the board
MCLK5: R15.2; also elsewhere on the board
MCLK6: R16.2; also elsewhere on the board
MCLK7: R17.2; also elsewhere on the board
unnamed: J1.D30 (TDI), R1.1
unnamed: J1.D31 (TDO), R1.2
unnamed: R10.1, U2.18 (1Y0)
unnamed: R11.1, U2.16 (1Y1)
unnamed: R12.1, U2.14 (1Y2)
unnamed: R13.1, U2.12 (1Y3)
unnamed: R14.1, U2.3 (2Y0)
unnamed: R15.1, U2.5 (2Y1)
unnamed: R16.1, U2.7 (2Y2)
unnamed: R17.1, U2.9 (2Y3)
unnamed: R20.1, U3.18 (1Y0)
unnamed: R21.1, U3.16 (1Y1)
unnamed: R22.1, U3.14 (1Y2)
unnamed: R23.1, U3.12 (1Y3)
unnamed: R24.1, U3.3 (2Y0)
unnamed: R25.1, U3.5 (2Y1)
unnamed: R26.1, U3.7 (2Y2)
unnamed: R27.1, U3.9 (2Y3)
SCLK_A: R20.2, TP3.1 (1_1); also elsewhere on the board
SCLK_B: R24.2; also elsewhere on the board
SYNC_A_N: R23.2; also elsewhere on the board
SYNC_B_N: R27.2; also elsewhere on the board
VADJ: J1.G39 (VADJ), J1.H40 (VADJ); also elsewhere on the board

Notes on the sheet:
J1: FMC LPC to the ZC702 FMC1 (J3)
LA00..LA05 carry the ADC bus (bank 34, VADJ = 3.3 V). PRSNT_M2C_L to GND marks the card present; TDI-TDO through R1 keeps the carrier's JTAG chain closed. 12P0V feeds the buck, VADJ the digital side (DVDD), 3P3VAUX the FRU EEPROM.
U1: FRU EEPROM
I2C address 0x50 (SOT-23 part, fixed address; GA0/GA1 unused). The carrier provides the I2C pull-ups.
X1: ADC clock
One oscillator for all eight converters (MCLK2, firmware: external clock), buffered 1:8 by U2.
U2: MCLK buffer, 1 to 8
33 R series at the driver to each AD7190 MCLK2.
U3: SPI buffer, groups A (ADC 0..3) and B (ADC 4..7)
Section 1 drives ADC 0..3 (group A), section 2 ADC 4..7 (group B), 33 R series at the driver. 10k pull-ups hold all four inputs high while the FPGA is unconfigured: converters idle and deselected, no floating CMOS inputs. DOUT/RDY returns unbuffered from each converter (33 R at the converter, chann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
Test points

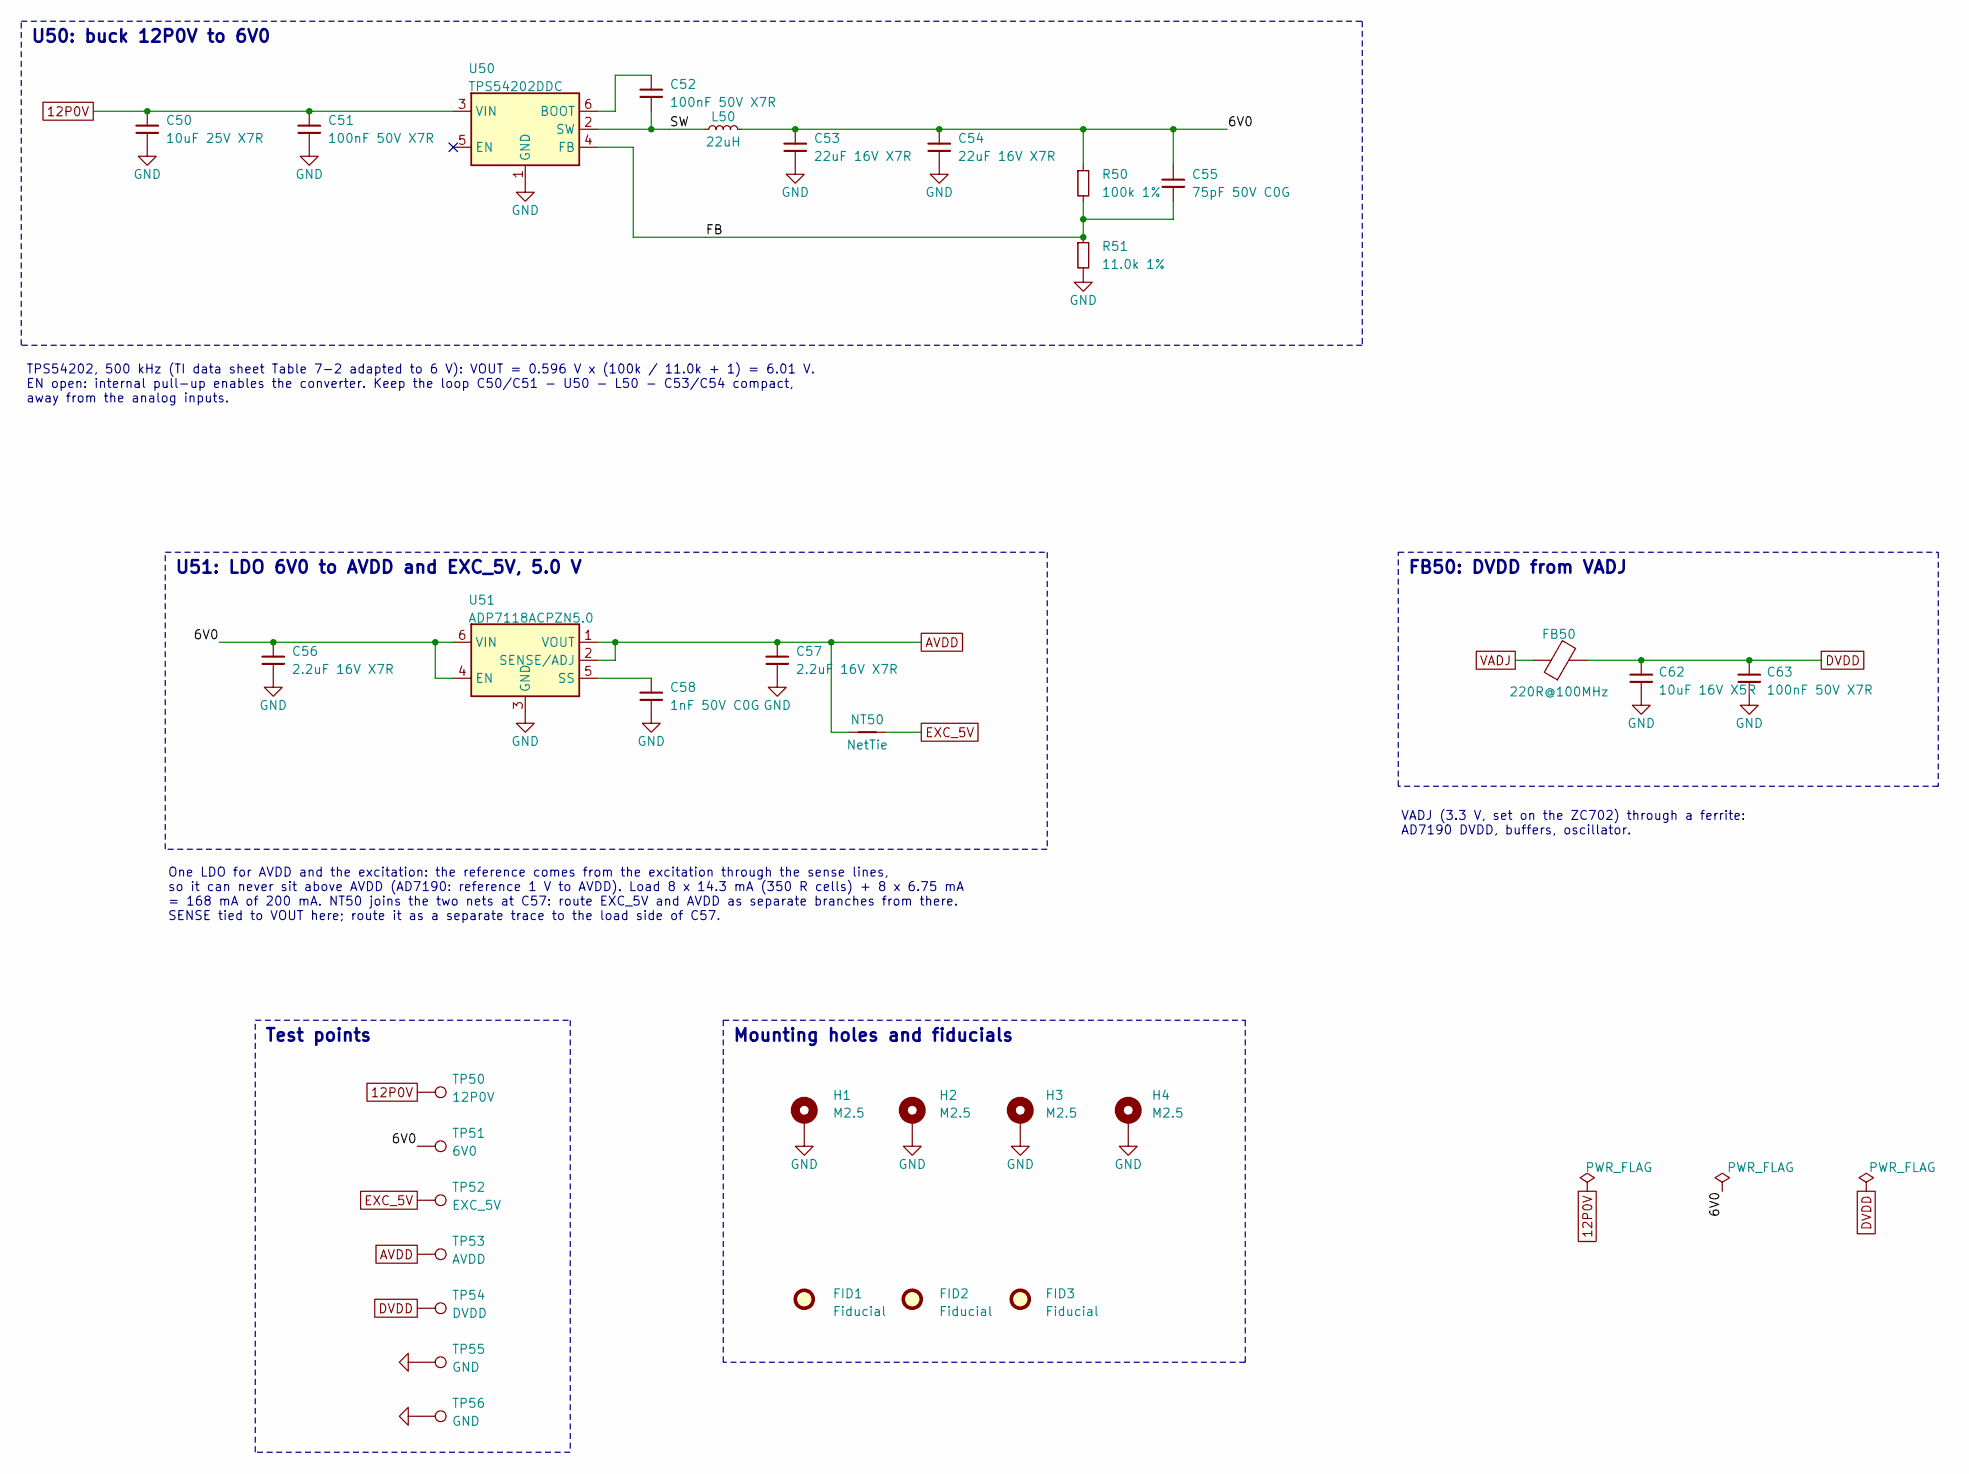
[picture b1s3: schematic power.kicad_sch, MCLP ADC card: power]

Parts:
C50: 10uF 25V X7R; C_1206_3216Metric
C51, C52, C63: 100nF 50V X7R; C_0603_1608Metric
C53, C54: 22uF 16V X7R; C_1206_3216Metric
C55: 75pF 50V C0G; C_0603_1608Metric
C56, C57: 2.2uF 16V X7R; C_0603_1608Metric
C58: 1nF 50V C0G; C_0603_1608Metric
C62: 10uF 16V X5R; C_0805_2012Metric
FB50: 220R@100MHz; L_0603_1608Metric; MPN Murata BLM18PG221SN1D
FID1, FID2, FID3: Fiducial; Fiducial_1mm_Mask2mm
H1, H2, H3, H4: M2.5; MountingHole_2.7mm_M2.5_Pad_Via
L50: 22uH; L_Bourns_SRN6045TA; MPN Bourns SRN6045TA-220M (22 uH, Isat >= 1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
NT50: NetTie; NetTie-2_SMD_Pad0.5mm
R50: 100k 1%; R_0603_1608Metric
R51: 11.0k 1%; R_0603_1608Metric
TP50: 12P0V; TestPoint_Pad_D1.5mm
TP51: 6V0; TestPoint_Pad_D1.5mm
TP52: EXC_5V; TestPoint_Pad_D1.5mm
TP53: AVDD; TestPoint_Pad_D1.5mm
TP54: DVDD; TestPoint_Pad_D1.5mm
TP55, TP56: GND; TestPoint_THTPad_D2.0mm_Drill1.0mm
U50: TPS54202DDC; SOT-23-6; MPN TI TPS54202DDCR
U51: ADP7118ACPZN5.0; LFCSP-6-1EP_2x2mm_P0.65mm_EP1x1.6mm; MPN ADI ADP7118ACPZN5.0-R7 (fixed 5.0 V; co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

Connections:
12P0V: C50.1, C51.1, TP50.1 (1_1), U50.3 (VIN); also elsewhere on the board
/Power/6V0: C53.1, C54.1, C55.1, C56.1, L50.2, R50.1, TP51.1 (1_1), U51.4 (EN), U51.6 (VIN)
/Power/FB: C55.2, R50.2, R51.1, U50.4 (FB)
/Power/SW: C52.2, L50.1, U50.2 (SW)
AVDD: C57.1, NT50.1, TP53.1 (1_1), U51.1 (VOUT), U51.2 (SENSE/ADJ); also elsewhere on the board
DVDD: C62.1, C63.1, FB50.2, TP54.1 (1_1); also elsewhere on the board
EXC_5V: NT50.2, TP52.1 (1_1); also elsewhere on the board
GND: C50.2, C51.2, C53.2, C54.2, C56.2, C57.2, C58.2, C62.2, C63.2, H1.1 (1_1), H2.1 (1_1), H3.1 (1_1), H4.1 (1_1), R51.2, TP55.1 (1_1), TP56.1 (1_1), U50.1 (GND), U51.3 (GND), U51.7 (GND); also elsewhere on the board
unnamed: C52.1, U50.6 (BOOT)
unnamed: C58.1, U51.5 (SS)
VADJ: FB50.1; also elsewhere on the board

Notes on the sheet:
U50: buck 12P0V to 6V0
TPS54202, 500 kHz (TI data sheet Table 7-2 adapted to 6 V): VOUT = 0.596 V x (100k / 11.0k + 1) = 6.01 V. EN open: internal pull-up enables the converter. Keep the loop C50/C51 - U50 - L50 - C53/C54 compact, away from the analog inputs.
U51: LDO 6V0 to AVDD and EXC_5V, 5.0 V
One LDO for AVDD and the excitation: the reference comes from the excitation through the sense lines, so it can never sit above AVDD (AD7190: reference 1 V to AVDD). Load 8 x 14.3 mA (350 R cells) + 8 x 6.75 mA = 168 mA of 200 mA. NT50 joins the two nets at C57: route EXC_5V and AVDD as separate br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
Test points
Mounting holes and fiducials
FB50: DVDD from VADJ
VADJ (3.3 V, set on the ZC702) through a ferrite: AD7190 DVDD, buffers, oscillator.
